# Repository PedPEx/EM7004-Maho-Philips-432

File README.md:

# EM7004-Maho-Philips-432 (ABORTED)
Retrofit analog interface adaptor for Maho CNC machines with a Philips 432/10 controller for use with a [Beckhoff EM7004](https://www.beckhoff.com/de-de/produkte/i-o/ethercat-klemmen/el-elm7xxx-kompakte-antriebstechnik/em7004.html) 

This project is used in the [Maho400E-LinuxCNC Retrofit project](https://github.com/PedPEx/Maho400E-LinuxCNC).

## Archiving
This project is being archived due to the EM7004 just having a 16 bit wide counter. With a travel-path of up to ~400 mm with a resolution of 1 µm a counter of at least 
```math 
n_{min} = \log_2 (\frac{400 mm}{1 \mu m}) = 18.61 bit \approx 19 bit 
```
The functionality of the rest of the PCB was not tested (BuckConverter is working). I'm sorry for everyone who had high hopes for this project or planned to use the finished product.

## Milestones
accomplished Milestones / ToDo:
- ✅ ready to go prototype at hand (v0.9.2 - corrected)
- ✅ working buck converter
- 🔲 tested with Maho axis attached
    - 🔲 working glass scale readout
    - 🔲 working Indramat speed controll

## Powering
The board needs a seperate supply voltage input to power the Philips converter-board (similar to Heidenhain EXE) for the encoders. The 5 V regulator is based around a [Texas Instruments LM33630](https://www.ti.com/product/LMR33630) and onboard. The BuckConverter part is based on the design from this [repository](https://github.com/PedPEx/BuckConverter_Enable). I recommend the [Phoenix Contact - 1962600 - TFKC 2,5/ 2-ST-5,08](https://www.phoenixcontact.com/de-de/produkte/leiterplattenstecker-tfkc-25-2-st-508-1962600) connectors to simply daisy chain all EM7004 24 V power supply lines.

## Usage
The pcb can be pretty easily assembled with standard parts of of LCSC (for furter information look at the [Online BOM](#online-preview--bom)). The connectors on the other side for plugging into the Beckhoff Module on the other hand are somewhat special. Unfortunately i found not a single alternative to the [Phoenix Contact - 1830498 - IMC 1,5/10-G-3,5 P20 THR](https://www.phoenixcontact.com/de-de/produkte/leiterplattengrundleiste-imc-1510-g-35-p20-thr-1830498) connectors, and these are not cheap at all. You can get five of them for free for testing purposes.

The first batch of boards is used in the testbench for the [Maho400E-LinuxCNC Retrofit project](https://github.com/PedPEx/Maho400E-LinuxCNC). LCSC did have a fault in the footprint files of the DB15 connectors, they were mirrored by accident. The fault has been fixed in v0.9.3 and the connectors were placed on the underside of the PCB in order to test the boards for functionality.

## Saving costs
In order to save some money, a JST right beside the 24V input connector is provided to power other adaptors and not needing an additional buck converter onboard of the other PCBs. Just daisy chain all adaptor interfaces. The BOM needs to be adjusted accordingly for that use case (ToDo).

## Limitations
In our Maho 400E with the original Philips 432/10 controller the encoder converter card is labeled "Maho 27.69 658" on the top and no label on the bottom. It seems to be a standard Heidenhain part (Part#: 229 281 01). Example pictures are avaliable [here](https://www.cnc-shopping.com/en/philips-432-cnc-heidenhain-229-281-01-exe-platine-maho-27-69-658-3-axis-615dc0edd3849-p-5395.html). This project is specifically meant to be used with this MAHO part!

Keep in mind this adaptor is not suited for use with a standard [Heidenhain EXE 600/900](https://cncbote.de/artikel/heidenhain-exe-600-5-f-id-nr-172680a/) series converter. These need an extra 12 V supply and other connectors.

## Online Preview / BOM / Schematic
[Online BOM](https://htmlpreview.github.io/?https://raw.githubusercontent.com/PedPEx/EM7004-Maho-Philips-432/main/bom/webviewer-BOM.html)

[PDF Schematic](https://github.com/PedPEx/EM7004-Maho-Philips-432/blob/main/EM7004-Maho-AxisAdaptor.pdf)

## Software part
This board is meant to be used with a EM7004 module and LinuxCNC. The LinuxCNC software part can be found here: [Maho400E-LinuxCNC](https://github.com/PedPEx/Maho400E-LinuxCNC)

## Note
The pictures were rendered with the help of Blender and the [pcb2blender](https://github.com/30350n/pcb2blender) plugin and the HTML BOM was created with [InteractiveHtmlBom](https://github.com/openscopeproject/InteractiveHtmlBom).

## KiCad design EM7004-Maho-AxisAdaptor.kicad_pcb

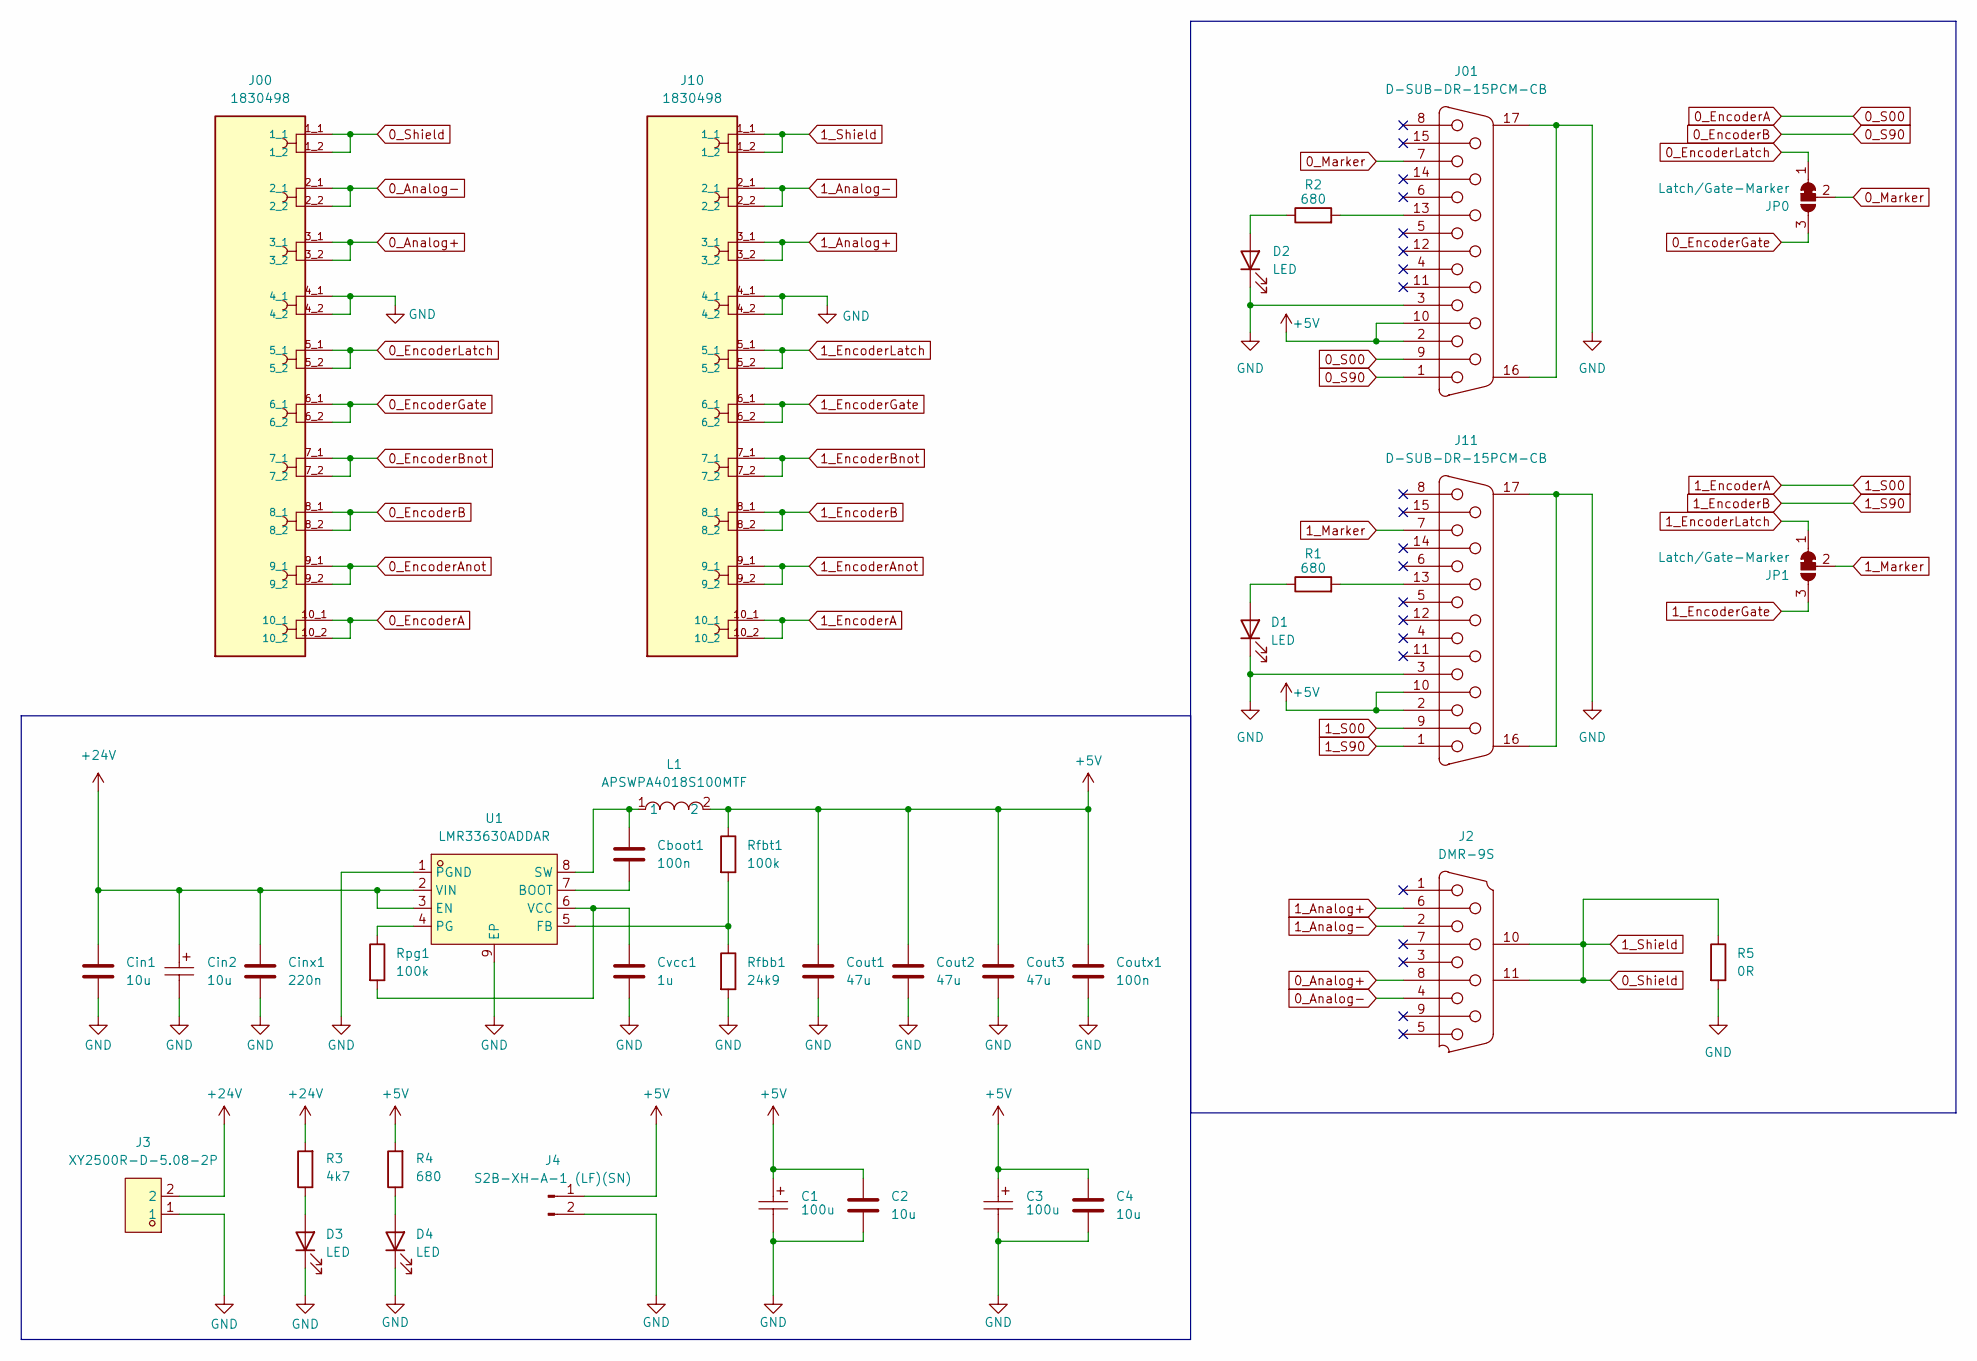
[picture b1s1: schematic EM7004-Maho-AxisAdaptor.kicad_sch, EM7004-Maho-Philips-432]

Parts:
C1, C3: 100u; CASE-D_7343; LCSC Part C8025
C2, C4: 10u; C_1210_3225Metric; LCSC Part C138687
Cboot1: 100n; C_0603_1608Metric; LCSC Part C14663
Cin1: 10u; C_1210_3225Metric; LCSC Part C138687
Cin2: 10u; CAP-SMD_L7.3-W4.3-R-RD; LCSC Part C117038
Cinx1: 220n; C_0805_2012Metric; LCSC Part C5378
Cout1, Cout2, Cout3: 47u; C_1206_3216Metric; LCSC Part C412300
Coutx1: 100n; C_0805_2012Metric
Cvcc1: 1u; C_0603_1608Metric; LCSC Part C5199872
D1, D2, D3, D4: LED; LED_0603_1608Metric
J00, J10: 1830498; PHOENIX_1830498
J01, J11: D-SUB-DR-15PCM-CB; DSUB-TH_XUNPU_D-SUB-DR-15PCM-CB; LCSC Part C19077338
J2: DMR-9S; DSUB-TH_DMR-9S; LCSC Part C141882
J3: XY2500R-D-5.08-2P; CONN-TH_2P-P5.08_XY2500R-D5.08-2P; LCSC Part C505824
J4: S2B-XH-A-1 (LF)(SN); CONN-TH_S2B-XH-A-1-LF-SN; LCSC Part C163035
JP0, JP1: Latch/Gate-Marker; SolderJumper-3_P1.3mm_Bridged12_Pad1.0x1.5mm
L1: APSWPA4018S100MTF; IND-SMD_L4.0-W4.0; LCSC Part C5363859
R1, R2, R4: 680; R_0603_1608Metric
R3: 4k7; R_0603_1608Metric
R5: 0R; R_0603_1608Metric
Rfbb1: 24k9; C_0603_1608Metric; LCSC Part C25962
Rfbt1: 100k; C_0603_1608Metric; LCSC Part C25803
Rpg1: 100k; C_0603_1608Metric; LCSC Part C25803
U1: LMR33630ADDAR; ESOP-8_L4.9-W3.9-P1.27-LS6.0-TL-EP; LCSC Part C841384

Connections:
0_Analog+: J00.3_1, J00.3_2, J2.8
0_Analog-: J00.2_1, J00.2_2, J2.4
0_EncoderA: J00.10_1, J00.10_2, J01.9
0_EncoderAnot: J00.9_1, J00.9_2
0_EncoderB: J00.8_1, J00.8_2, J01.1
0_EncoderBnot: J00.7_1, J00.7_2
0_EncoderGate: J00.6_1, J00.6_2, JP0.3 (B)
0_EncoderLatch: J00.5_1, J00.5_2, JP0.1 (A)
0_Marker: J01.7, JP0.2 (C)
0_Shield: J00.1_1, J00.1_2, J2.10 (MH1), J2.11 (MH2), J10.1_1, J10.1_2, R5.1
1_Analog+: J2.6, J10.3_1, J10.3_2
1_Analog-: J2.2, J10.2_1, J10.2_2
1_EncoderA: J10.10_1, J10.10_2, J11.9
1_EncoderAnot: J10.9_1, J10.9_2
1_EncoderB: J10.8_1, J10.8_2, J11.1
1_EncoderBnot: J10.7_1, J10.7_2
1_EncoderGate: J10.6_1, J10.6_2, JP1.3 (B)
1_EncoderLatch: J10.5_1, J10.5_2, JP1.1 (A)
1_Marker: J11.7, JP1.2 (C)
+5V: C1.1, C2.1, C3.1, C4.1, Cout1.1, Cout2.1, Cout3.1, Coutx1.1, J01.2, J01.10, J4.1, J11.2, J11.10, L1.2, R4.2, Rfbt1.1
+24V: Cin1.1, Cin2.1, Cinx1.1, J3.2, R3.2, U1.2 (VIN), U1.3 (EN)
GND: C1.2, C2.2, C3.2, C4.2, Cin1.2, Cin2.2, Cinx1.2, Cout1.2, Cout2.2, Cout3.2, Coutx1.2, Cvcc1.2, D1.1 (K), D2.1 (K), D3.1 (K), D4.1 (K), J00.4_1, J00.4_2, J01.3, J01.16 (MH2), J01.17 (MH1), J3.1, J4.2, J10.4_1, J10.4_2, J11.3, J11.16 (MH2), J11.17 (MH1), R5.2, Rfbb1.2, U1.1 (PGND), U1.9 (EP)
unnamed: D1.2 (A), R1.1
unnamed: D2.2 (A), R2.1
unnamed: D3.2 (A), R3.1
unnamed: D4.2 (A), R4.1
unnamed: J01.13, R2.2
unnamed: J11.13, R1.2
unnamed: Cboot1.2, U1.7 (BOOT)
unnamed: Rfbb1.1, Rfbt1.2, U1.5 (FB)
unnamed: Rpg1.1, U1.4 (PG)
unnamed: Cboot1.1, L1.1, U1.8 (SW)
unnamed: Cvcc1.1, Rpg1.2, U1.6 (VCC)

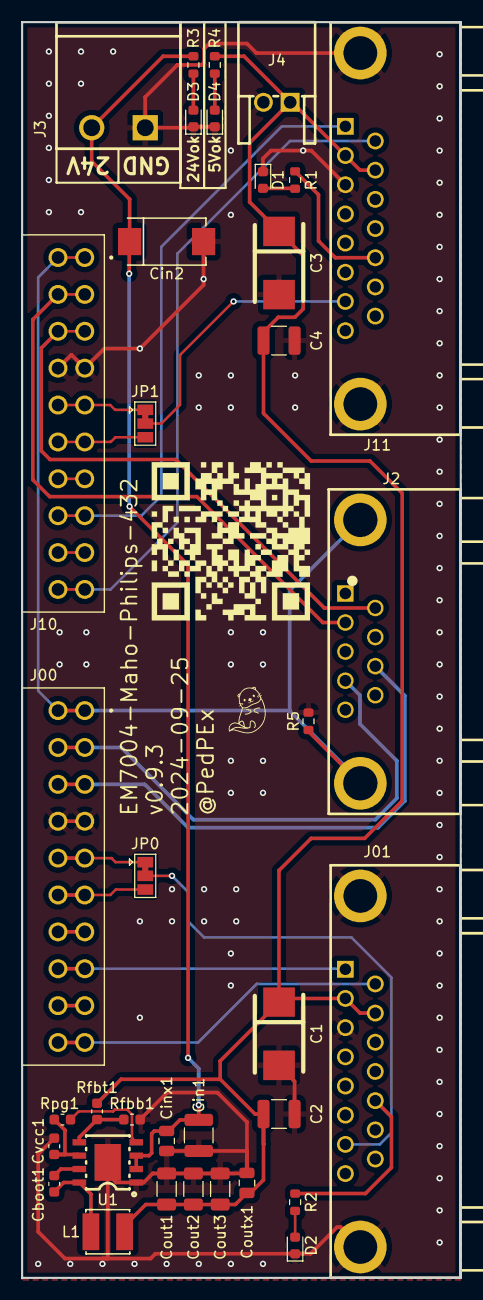
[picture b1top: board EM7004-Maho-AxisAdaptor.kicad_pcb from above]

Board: 2 copper layers, 41.6 x 119.2 mm, 36 parts (0 on the bottom side), 33 nets.

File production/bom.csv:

Designator,Footprint,Quantity,Value,LCSC Part #
"C1, C3",CASE-D_7343,2,100u,C8025
"C2, C4, Cin1",1210,3,10u,C138687
Cboot1,0603,1,100n,C14663
Cin2,CAP-SMD_L7.3-W4.3-R-RD,1,10u,C117038
Cinx1,0805,1,220n,C5378
"Cout1, Cout2, Cout3",1206,3,47u,C412300
Coutx1,0805,1,100n,
Cvcc1,0603,1,1u,C5199872
"D1, D2, D3, D4",0603,4,LED,
"J00, J10",PHOENIX_1830498,2,1830498,
"J01, J11",DSUB-TH_XUNPU_D-SUB-DR-15PCM-CB,2,D-SUB-DR-15PCM-CB,C19077338
J2,DSUB-TH_DMR-9S,1,DMR-9S,C141882
J3,CONN-TH_2P-P5.08_XY2500R-D5.08-2P,1,XY2500R-D-5.08-2P,C505824
J4,CONN-TH_S2B-XH-A-1-LF-SN,1,S2B-XH-A-1 (LF)(SN),C163035
L1,IND-SMD_L4.0-W4.0,1,APSWPA4018S100MTF,C5363859
"R1, R2, R4",0603,3,680,
R3,0603,1,4k7,
R5,0603,1,0R,
Rfbb1,0603,1,24k9,C25962
"Rfbt1, Rpg1",0603,2,100k,C25803
U1,ESOP-8_L4.9-W3.9-P1.27-LS6.0-TL-EP,1,LMR33630ADDAR,C841384

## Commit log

2024-04-15 init project
2024-04-15 added HTML-BOM and 3D file (.step)
2024-04-15 fixed typo
2024-04-15 fixed broken links
2024-04-15 fixed links, removed 3D model link
2024-08-13 added 5V regulator
2024-08-14 corrected LED labels
2024-08-15 added renders and updated readme
2024-09-13 finalized v0.9.2 design
2024-09-13 corrected pdf link
2024-09-26 v0.9.3 - mirrored LCSC part C19077338 (DB15 connectors) was corrected
2025-04-09 added pictures assembled & installed PCB
2025-05-15 last commit before archiving
